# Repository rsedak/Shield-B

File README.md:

[Croatian version](README_HR-HR.md).

Introduction
============

Shield-B v1.2 is version of Arduino Uno based shield for student education compatible with BASCOM-AVR(C) and Arduino IDE.
During programming please keep in mind next design rules:
- D2, D4, D7, D8 — control step motor (J6)
- D5 — control DC motor (M1)
- D6 — control DC motor (M2)
- D9 — control servo motor (J5)
- D10 — control servo motor (J8)
- D13 — reserved for buzzer
- A0 — reserved for potentiometer RV1
- A1 — reserved for potentiometer RV2
- A2 — reserved for switch SW2 in INPUT_PULLUP mode
- A3 — reserved for switch SW3 INPUT_PULLUP mode
- A4,A5 — reserved for I2C communication with on board pull-up resistors (J7)

Contributors
------------
- Robert Sedak — features, Arduino expertise, schematic design, CAD design.
- Vladimir Mitrović — features, BASCOM-AVR expertise

Application
-----------
Robert Sedak made a video with examples programmed in Arduino IDE:

You can download examples for Arduino IDE from [here](examples/).

Bill Of Materials
-----------------
- 1 ea., PCB
- 1 ea., 680R ohm 1/4W 1% Resistor (R1)
- 8 ea., 1K ohm 1/4W 1% Resistor (R2-R8, R14)
- 2 ea., 10K ohm 1/4W 1% Resistor (R9, R10)
- 2 ea., 100R ohm 1/4W 1% Resistor (R11, R12)
- 1 ea., 1.5K ohm 1/4W 1% Resistor (R13)
- 1 ea., LED 5mm DUAL AKA (D1)
- 8 ea., LED 3mm (D2-D8, D10)
- 1 ea., 1N5817 (D9)
- 1 ea., 100nF (C1-C3)
- 1 ea., 14x7.5mm passive electronic piezoelectric buzzer SE (BZ1)
- 1 ea., Barrel Jack switch (J1)
- 3 ea., Screw terminal 2Pin (J2-J4)
- 2 ea., 1x3Pin 2.54mm Straight Pin Header - Black (J5, J8)
- 1 ea., Connector JST_XH_B5B-XH-A (J6)
- 1 ea., 1x4 pin 2.54mm Socket Connector - horizontal (J7)
- 2 ea., RV09 10K potentiometer - long shaft (RV1, RV2)
- 1 ea., 6x3x4.3mm SPST Momentary push switch (SW1)
- 2 ea., 6x6x10mm SPST Momentary push switch (SW1, SW2)
- 1 ea., 1x10Pin 2.54mm Straight Pin Header - Black
- 2 ea., 1x8Pin 2.54mm Straight Pin Header - Black
- 1 ea., 1x6Pin 2.54mm Straight Pin Header - Black
- 1 ea., 8 pin DIP Socket
- 1 ea., L272M
- 1 ea., 16 pin DIP Socket
- 1 ea., ULN2003

Design Files
------------
This project is designed using Open Source [KiCad](http://kicad.org/). Design files are located in the [design_files](design_files/) folder.  You can see the [schematic](images/shield-b_schematic.png).

Gerber files
------------
You can download gerber files from [here](gerber/shield_b_v1.2.zip).

Firmware
--------
This project can be programmed using the Open Source [Arduino](https://www.arduino.cc/) and [BASCOM-AVR(C)](https://www.mcselec.com/index.php?option=com_content&task=view&id=14&Itemid=103).
Arduino examples are located in [examples](examples/) folder.

License
-------
[Attribution-ShareAlike 4.0 International (CC BY-SA 4.0)](https://creativecommons.org/licenses/by-sa/4.0/)

You are free to:
- Share — copy and redistribute the material in any medium or format
- Adapt — remix, transform, and build upon the material

This license is acceptable for Free Cultural Works.
- The licensor cannot revoke these freedoms as long as you follow the license terms.

Under the following terms:
- Attribution — You must give appropriate credit, provide a link to the license, and indicate if changes were made. You may do so in any reasonable manner, but not in any way that suggests the licensor endorses you or your use.
- ShareAlike — If you remix, transform, or build upon the material, you must distribute your contributions under the same license as the original.

No additional restrictions — You may not apply legal terms or technological measures that legally restrict others from doing anything the license permits.

Reference Designs ARE PROVIDED "AS IS" AND "WITH ALL FAULTS". Authors DISCLAIMS ALL OTHER WARRANTIES, EXPRESS OR IMPLIED, REGARDING PRODUCTS, INCLUDING BUT NOT LIMITED TO, ANY IMPLIED WARRANTIES OF MERCHANTABILITY OR FITNESS FOR A PARTICULAR PURPOSE.
Authors may make changes to specifications and product descriptions at any time, without notice. The Customer must notrely on the absence or characteristics of any features or instructions marked "reserved" or "undefined." 
Authors reservesthese for future definition and shall have no responsibility whatsoever for conflicts or incompatibilities arising from future changes to them. The product information on the Web Site or Materials is subject to change without notice. Do not finalize a design with this info.

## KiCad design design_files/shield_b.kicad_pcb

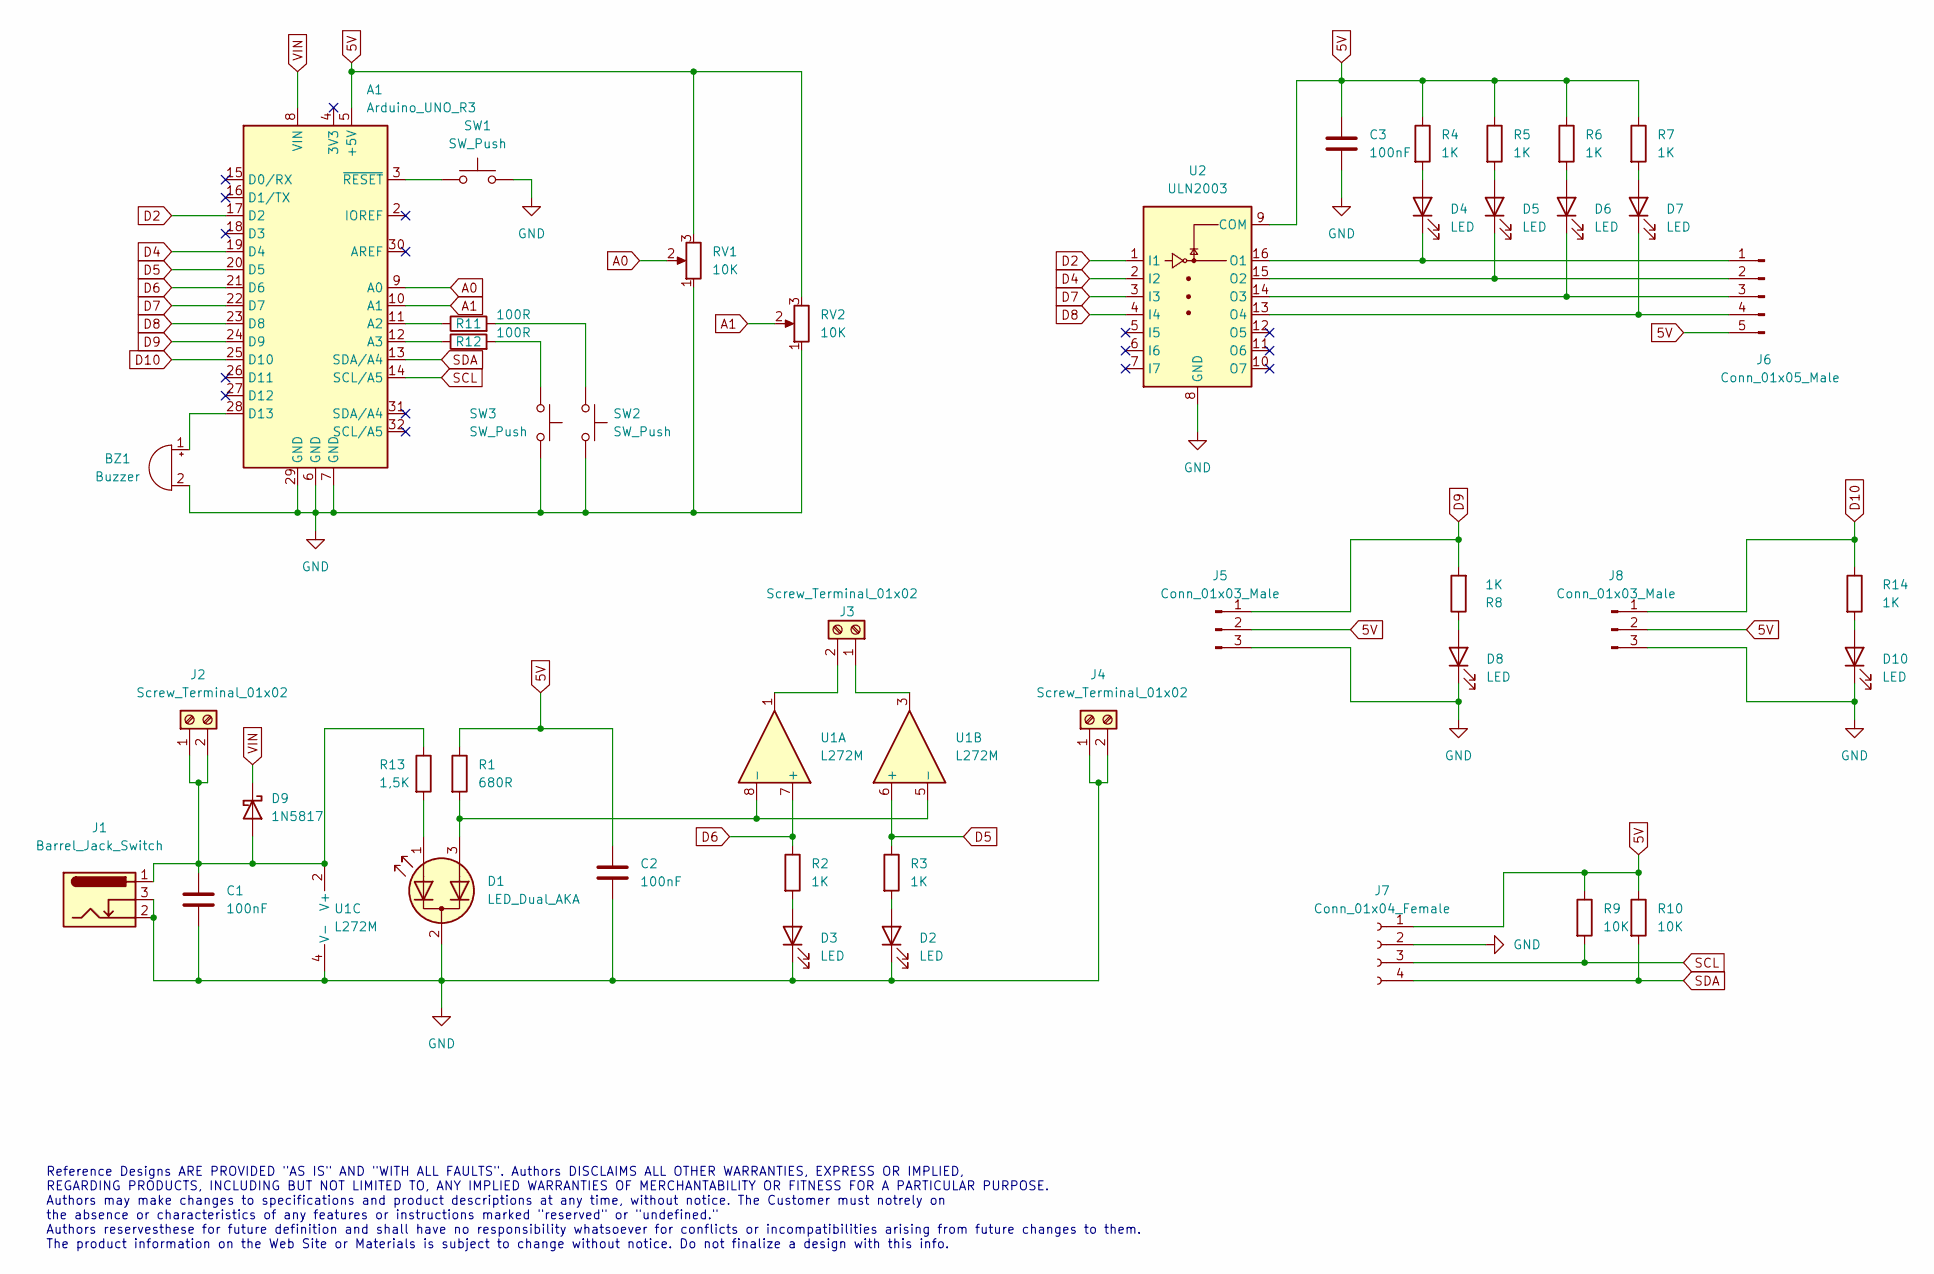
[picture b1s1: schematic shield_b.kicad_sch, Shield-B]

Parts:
A1: Arduino_UNO_R3
BZ1: Buzzer; Buzzer_12x9.5RM7.6_5
C1, C2, C3: 100nF; C_Disc_D5.0mm_W2.5mm_P5.00mm
D1: LED_Dual_AKA; LED_D5.0mm-3
D2, D3, D4, D5, D6, D7, D8, D10: LED; LED_D3.0mm
D9: 1N5817; D_DO-41_SOD81_P10.16mm_Horizontal
J1: Barrel_Jack_Switch; BarrelJack_GCT_DCJ200-10-A_Horizontal
J2, J3, J4: Screw_Terminal_01x02; TerminalBlock_bornier-2_P5.08mm
J5, J8: Conn_01x03_Male; PinHeader_1x03_P2.54mm_Vertical
J6: Conn_01x05_Male; JST_XH_B5B-XH-A_1x05_P2.50mm_Vertical
J7: Conn_01x04_Female; PinSocket_1x04_P2.54mm_Horizontal
R1: 680R; R_Axial_DIN0207_L6.3mm_D2.5mm_P7.62mm_Horizontal
R2, R3, R4, R5, R6, R7, R8, R14: 1K; R_Axial_DIN0207_L6.3mm_D2.5mm_P7.62mm_Horizontal
R9, R10: 10K; R_Axial_DIN0207_L6.3mm_D2.5mm_P7.62mm_Horizontal
R11, R12: 100R; R_Axial_DIN0207_L6.3mm_D2.5mm_P7.62mm_Horizontal
R13: 1,5K; R_Axial_DIN0207_L6.3mm_D2.5mm_P7.62mm_Horizontal
RV1, RV2: 10K; Potentiometer_Alpha_RV09ACF-40_Single_Vertical
SW1: SW_Push; SW_PUSH_3x6x5mm
SW2, SW3: SW_Push; SW_PUSH_6mm
U1: L272M; DIP-8_W7.62mm_Socket
U2: ULN2003; DIP-16_W7.62mm_Socket

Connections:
5V: A1.5 (+5V), C2.1, C3.2, J5.2, J6.5, J7.1, J8.2, R1.1, R4.1, R5.1, R6.1, R7.1, R9.1, R10.1, RV1.3, RV2.3, U2.9 (COM)
A0: A1.9 (A0), RV1.2
A1: A1.10 (A1), RV2.2
D2: A1.17 (D2), U2.1 (I1)
D4: A1.19 (D4), U2.2 (I2)
D5: A1.20 (D5), R3.1, U1.6 (+)
D6: A1.21 (D6), R2.1, U1.7 (+)
D7: A1.22 (D7), U2.3 (I3)
D8: A1.23 (D8), U2.4 (I4)
D9: A1.24 (D9), J5.1, R8.2
D10: A1.25 (D10), J8.1, R14.1
GND: A1.6 (GND), A1.7 (GND), A1.29 (GND), BZ1.2 (+), C1.2, C2.2, C3.1, D1.2 (K), D2.1 (K), D3.1 (K), D8.1 (K), D10.1 (K), J1.2, J1.3, J4.1, J4.2, J5.3, J7.2, J8.3, RV1.1, RV2.1, SW1.2, SW2.2, SW3.2, U1.4 (V-), U2.8 (GND)
unnamed: A1.3 (~RESET), SW1.1
unnamed: A1.11 (A2), R11.1
unnamed: A1.12 (A3), R12.1
unnamed: A1.28 (D13), BZ1.1 (-)
unnamed: C1.1, D9.2 (A), J1.1, J2.1, J2.2, R13.1, U1.2 (V+)
unnamed: D1.1 (A1), R13.2
unnamed: D1.3 (A2), R1.2, U1.5 (-), U1.8 (-)
unnamed: D2.2 (A), R3.2
unnamed: D3.2 (A), R2.2
unnamed: D4.1 (K), J6.1, U2.16 (O1)
unnamed: D4.2 (A), R4.2
unnamed: D5.1 (K), J6.2, U2.15 (O2)
unnamed: D5.2 (A), R5.2
unnamed: D6.1 (K), J6.3, U2.14 (O3)
unnamed: D6.2 (A), R6.2
unnamed: D7.1 (K), J6.4, U2.13 (O4)
unnamed: D7.2 (A), R7.2
unnamed: D8.2 (A), R8.1
unnamed: D10.2 (A), R14.2
unnamed: J3.1, U1.3
unnamed: J3.2, U1.1
unnamed: R11.2, SW2.1
unnamed: R12.2, SW3.1
SCL: A1.14 (SCL/A5), J7.3, R9.2
SDA: A1.13 (SDA/A4), J7.4, R10.2
VIN: A1.8 (VIN), D9.1 (K)

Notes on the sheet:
Reference Designs ARE PROVIDED "AS IS" AND "WITH ALL FAULTS". Authors DISCLAIMS ALL OTHER WARRANTIES, EXPRESS OR IMPLIED, REGARDING PRODUCTS, INCLUDING BUT NOT LIMITED TO, ANY IMPLIED WARRANTIES OF MERCHANTABILITY OR FITNESS FOR A PARTICULAR PURPOSE. Authors may make changes to specifications and p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

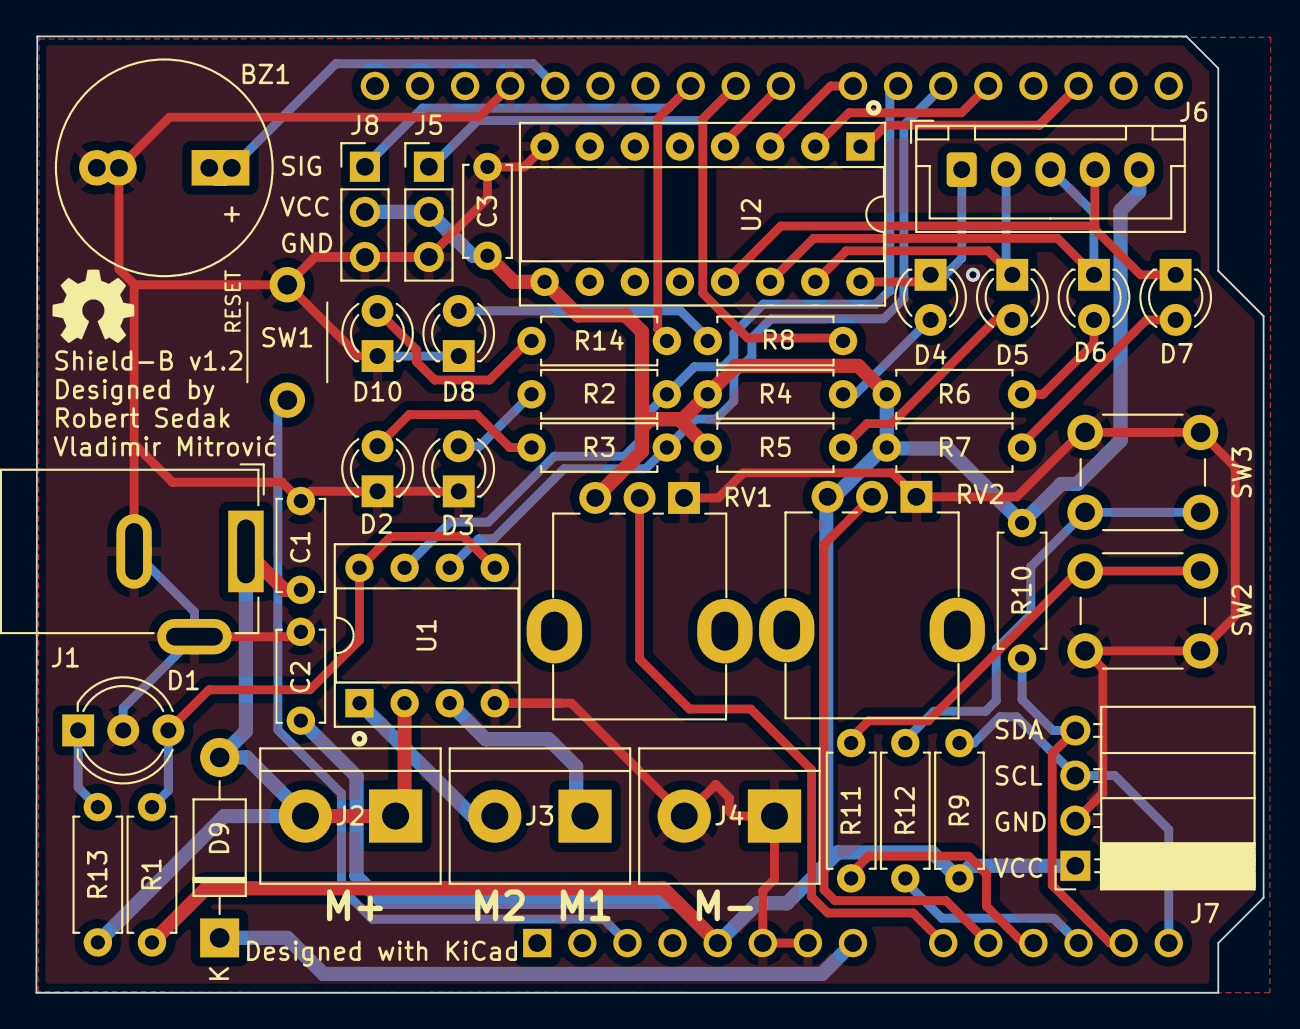
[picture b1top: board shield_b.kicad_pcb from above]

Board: 2 copper layers, 69.1 x 53.8 mm, 45 parts (1 on the bottom side), 38 nets.

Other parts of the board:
OSHW Logo: OSHW-Logo_6x6mm_SilkScreen

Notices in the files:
design_files/shield_b.kicad_pcb:
License: CC-BY-SA 4.0
